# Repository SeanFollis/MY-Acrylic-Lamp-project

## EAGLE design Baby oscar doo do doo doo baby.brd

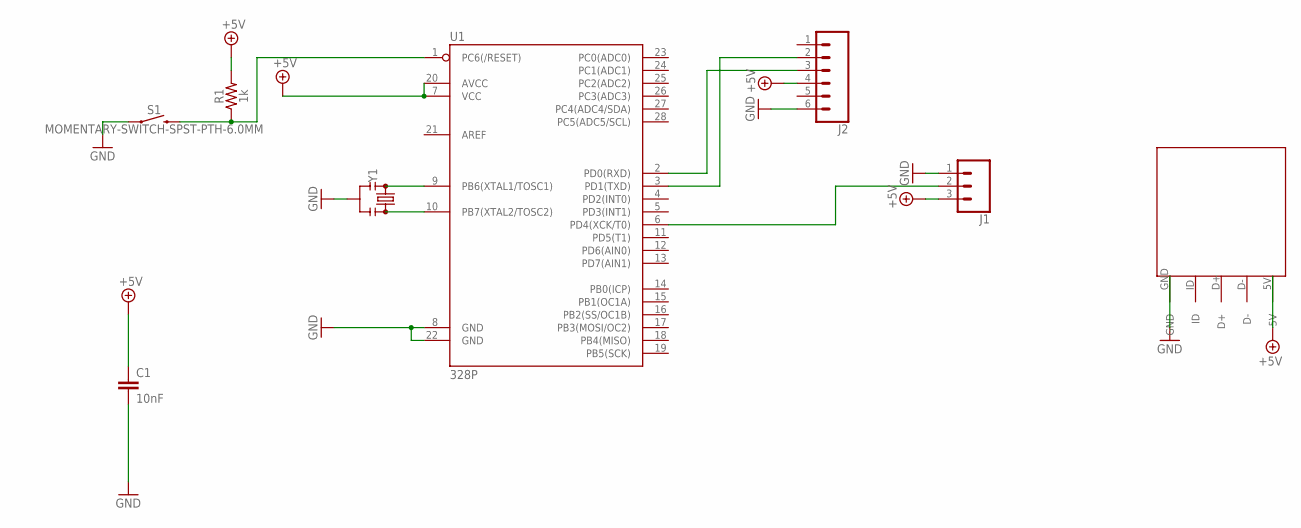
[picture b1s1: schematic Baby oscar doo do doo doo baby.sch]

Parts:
C1: 10nF; CAP-PTH-10MM
J1: CONN_03; 1X03
J2: CONN_06SILK_FEMALE_PTH; 1X06
R1: 1k; AXIAL-0.3
S1: MOMENTARY-SWITCH-SPST-PTH-6.0MM; TACTILE_SWITCH_PTH_6.0MM
U1: 328P; DIP28
U$1: USBCONNECTOR
Y1: RESONATORPTH-7.6X3.8; RESONATOR-PTH-7.6X3.8

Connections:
+5V: C1.1, J1.3, J2.4, R1.P$2 (2), U1.7 (VCC), U1.20 (AVCC), U$1.5V
GND: C1.2, J1.1, J2.6, S1.1, U1.8 (GND), U1.22 (GND), U$1.GND, Y1.2
unnamed: R1.P$1 (1), S1.3 (2), U1.1 (PC6(/RESET))
unnamed: U1.9 (PB6(XTAL1/TOSC1)), Y1.16MHZ (1)
unnamed: J2.2, U1.3 (PD1(TXD))
unnamed: U1.10 (PB7(XTAL2/TOSC2)), Y1.3
unnamed: J2.3, U1.2 (PD0(RXD))
unnamed: J1.2, U1.6 (PD4(XCK/T0))

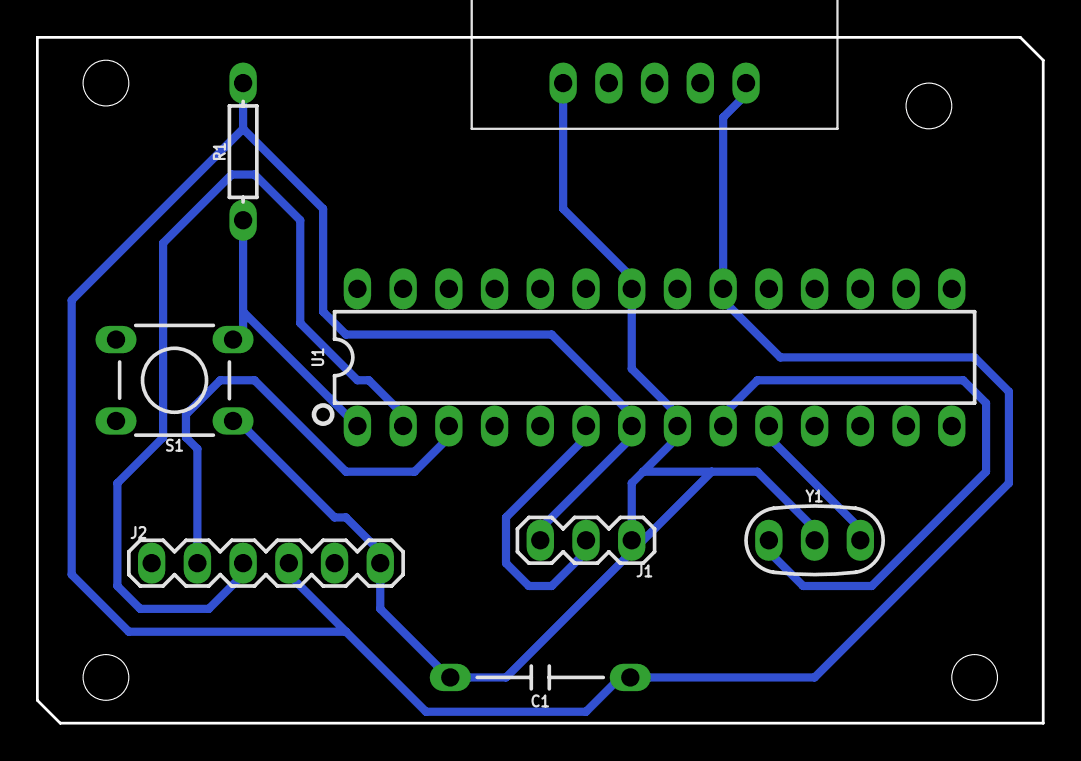
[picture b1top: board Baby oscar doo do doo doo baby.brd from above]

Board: 2 copper layers, 55.9 x 38.1 mm, 8 parts (0 on the bottom side), 8 nets.
